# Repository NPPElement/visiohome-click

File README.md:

# visiohome-click
The device turns a conventional non-latching electric switch into a smart

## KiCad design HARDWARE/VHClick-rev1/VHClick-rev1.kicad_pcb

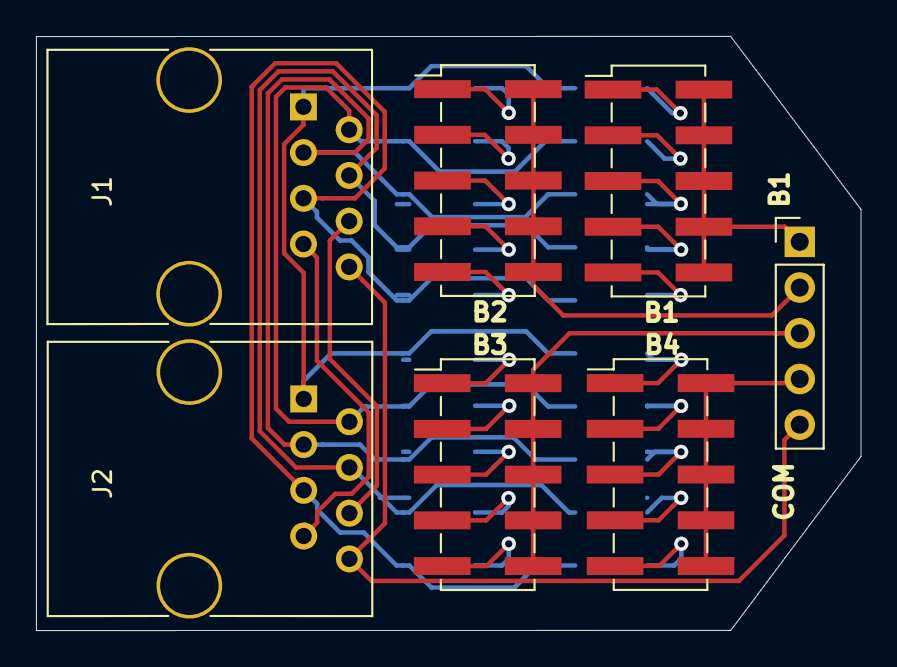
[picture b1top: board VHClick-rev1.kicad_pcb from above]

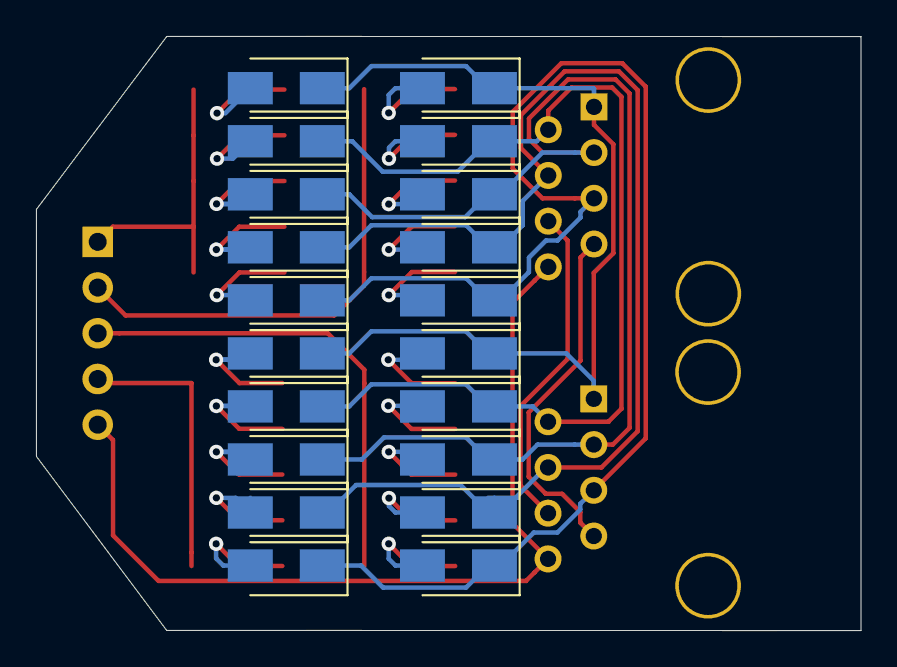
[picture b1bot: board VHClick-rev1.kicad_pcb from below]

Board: 2 copper layers, 45.8 x 33.0 mm, 27 parts (20 on the bottom side), 32 nets.

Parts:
B1, B2, B3, B4: 02x05; Pin_Header_Straight_2x05_Pitch2.54mm_SMD
B1#2: Conn_01x05; Pin_Header_Straight_1x05_Pitch2.54mm
D1, D2, D3, D4, D5, D6, D7, D8, D9, D10, D11, D12, D13, D14, D15, D16, D17, D18, D19, D20: SB160; D_SMA
J1, J2: RJ45; RJ45_8

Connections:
/BT-1: B1.2, B1.4, B1.6, B1.8, B1.10, B1#2.1
/BT-2: B1#2.2, B2.2, B2.4, B2.6, B2.8, B2.10
/BT-3: B1#2.3, B3.2, B3.4, B3.6, B3.8, B3.10
/BT-4: B1#2.4, B4.2, B4.4, B4.6, B4.8, B4.10
/IN-1: D1.1, D6.1, D11.1, D16.1, J1.1, J2.1
/IN-2: D2.1, D7.1, D12.1, D17.1, J1.2, J2.2
/IN-3: D3.1, D8.1, D13.1, D18.1, J1.3, J2.3
/IN-4: D4.1, D9.1, D14.1, D19.1, J1.4, J2.4
/IN-5: D5.1, D10.1, D15.1, D20.1, J1.5, J2.5
/IN-6: J1.6, J2.6
/IN-7: J1.7, J2.7
unnamed: B4.1, D1.2
unnamed: B4.3, D2.2
unnamed: B4.5, D3.2
unnamed: B4.7, D4.2
unnamed: B4.9, D5.2
unnamed: B3.1, D6.2
unnamed: B3.3, D7.2
unnamed: B3.5, D8.2
unnamed: B3.7, D9.2
unnamed: B3.9, D10.2
unnamed: B2.1, D11.2
unnamed: B2.3, D12.2
unnamed: B2.5, D13.2
unnamed: B2.7, D14.2
unnamed: B2.9, D15.2
unnamed: B1.1, D16.2
unnamed: B1.3, D17.2
unnamed: B1.5, D18.2
unnamed: B1.7, D19.2
unnamed: B1.9, D20.2
VPP: B1#2.5, J1.8, J2.8

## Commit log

2019-11-29 Rev1 - Prepared for Production
2019-11-29 Scheme .pdf
2019-12-01 Add img
2019-12-02 add png
